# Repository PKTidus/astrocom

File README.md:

# A.S.T.R.O.COM. - Advanced Solar Tracking and Rover Observation Communication

The ASTROCOM project, developed in collaboration with the [Florida Space Institute (FSI)](https://fsi.ucf.edu/), addresses the challenge of exploring permanently shaded regions on the lunar surface. Comprising of heliostat and communication beacon towers, ASTROCOM enables wireless transmission of power and information to and from rovers within these shaded areas. The Heliostat tower utilize a reflector to redirect sunlight into the craters, powering solar assets and illuminating shaded regions, while also enabling a communication network. A portable communication beacon, intended to be deployed by rovers, a facilitate communication between the heliostat towers and rovers, overcoming obstacles within the craters.
Heliostat Tower             |  Communication Beacon
:-------------------------:|:-------------------------:
  |  

**Project Members:**  
Alex Fiset (Power/PCB)  
Pedro Kasprzykowski (Wireless/Website)  
Stephen Martin (Sensors/Solar Tracking)  
Binh Pham (Project Lead/Motors)  

**Special Thanks:**  
Dr. Chung Yong Chan  
Dr. Arthur Weeks  

**This project was sponsored by the [Florida Space Institute](https://fsi.ucf.edu/)**  

**This project was made as a [University of Central Florida Electrical and Computer Engineering Department](https://www.ece.ucf.edu/) Senior Design project throughout the Fall 2023 - Spring 2024 term**

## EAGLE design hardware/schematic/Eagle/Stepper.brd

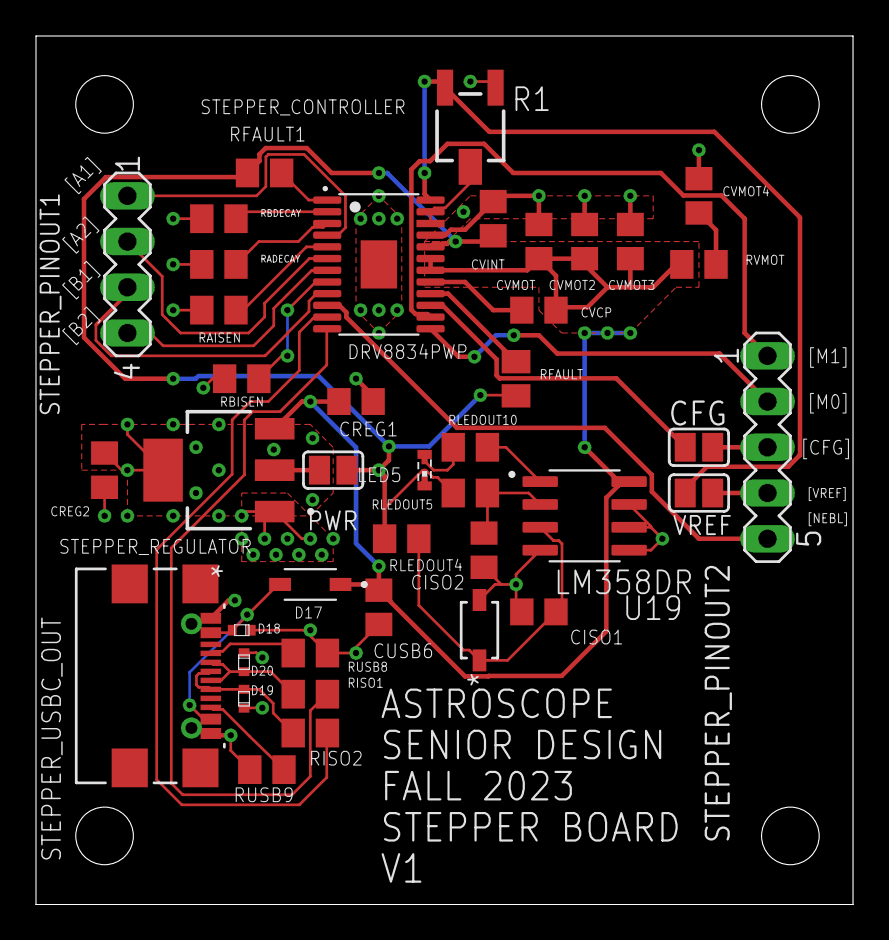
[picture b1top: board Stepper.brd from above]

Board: 2 copper layers, 45.4 x 48.2 mm, 41 parts (0 on the bottom side), 35 nets.

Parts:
CFG: SJ
CISO1, CISO2: 0.01uF; C0805
CREG1: 10uF; C0805
CREG2: 22uF; C0805
CUSB6: 10uF; C0805
CVCP: 0.01uF; C0805
CVINT: 4.7uF; C0805
CVMOT, CVMOT4: 10uF; C0805
CVMOT2, CVMOT3: 0.1uF; C0805
D17: 1N5819HW-7-F; SOD3715X145N
D18, D19, D20: CPDQ5V0-HF; MBTB-D-SOD-923F-IMP-0402
LED5: SMARTLED-TTW
PWR: SJ
R1: 10k; 3223G
RADECAY: 47k; M0805
RAISEN: 0.1; M0805
RBDECAY: 47k; M0805
RBISEN: 0.1; M0805
RFAULT: 1.5k; M0805
RFAULT1: 10k; M0805
RISO1, RISO2: 1.5k; M0805
RLEDOUT4, RLEDOUT5: 10k; M0805
RLEDOUT10: 2.2k; M0805
RUSB8, RUSB9: 5.1k; M0805
RVMOT: 1; M0805
STEPPER_CONTROLLER: DRV8834PWP; SOP65P640X120-25N
STEPPER_PINOUT1: MA04-1
STEPPER_PINOUT2: MA05-1
STEPPER_REGULATOR: AZ1117IH-3.3TRG1; SOT230P700X185-4N
STEPPER_USBC_OUT: USB4110-GF-A; USB4110-GF-A_GCT
U16: MMSZ5225BT1G; SOD-123_ONS
U19: LM358DR; SOIC127P599X175-8N
VREF: SJ

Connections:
3.3VOUTUSB2: CVINT.1, LED5.A@1, PWR.2, RFAULT.2, RFAULT1.1, RLEDOUT4.2, RLEDOUT5.2, STEPPER_CONTROLLER.20
3.3VREGOUT: CREG2.1, PWR.1, STEPPER_REGULATOR.2, STEPPER_REGULATOR.4
5VOUTUSB2: CREG1.1, CUSB6.1, CVCP.1, CVMOT.2, CVMOT2.2, CVMOT3.2, D17.C, RVMOT.2, STEPPER_CONTROLLER.18, STEPPER_CONTROLLER.19, STEPPER_REGULATOR.3, U19.8
AOUT1: STEPPER_CONTROLLER.4, STEPPER_PINOUT1.1
AOUT2: STEPPER_CONTROLLER.6, STEPPER_PINOUT1.2
BOUT1: STEPPER_CONTROLLER.9, STEPPER_PINOUT1.3
BOUT2: STEPPER_CONTROLLER.7, STEPPER_PINOUT1.4
CONFIGOUT: CFG.1, STEPPER_PINOUT2.3
GND: CISO1.2, CISO2.2, CREG1.2, CREG2.2, CUSB6.2, CVINT.2, CVMOT.1, CVMOT2.1, CVMOT3.1, CVMOT4.1, D18.1, D19.1, D20.1, R1.1, RADECAY.2, RAISEN.2, RBDECAY.2, RBISEN.2, RUSB8.2, RUSB9.2, STEPPER_CONTROLLER.21, STEPPER_CONTROLLER.25, STEPPER_REGULATOR.1, STEPPER_USBC_OUT.A1-B12, STEPPER_USBC_OUT.A12-B1, U16.2, U19.4, U19.5, U19.6, U19.7
GPIO8M: D19.2, RISO2.2, STEPPER_USBC_OUT.A6, STEPPER_USBC_OUT.B6
GPIO9M: D20.2, RISO1.2, STEPPER_USBC_OUT.A7, STEPPER_USBC_OUT.B7
M0OUT: STEPPER_CONTROLLER.13, STEPPER_PINOUT2.2
M1OUT: STEPPER_CONTROLLER.14, STEPPER_PINOUT2.1
unnamed: RISO1.1, STEPPER_CONTROLLER.12
unnamed: RISO2.1, STEPPER_CONTROLLER.11
unnamed: CVMOT4.2, RVMOT.1
unnamed: RBISEN.1, STEPPER_CONTROLLER.8
unnamed: RAISEN.1, STEPPER_CONTROLLER.5
unnamed: RBDECAY.1, STEPPER_CONTROLLER.2
unnamed: RADECAY.1, STEPPER_CONTROLLER.3
unnamed: RFAULT.1, STEPPER_CONTROLLER.16
unnamed: CVCP.2, STEPPER_CONTROLLER.17
unnamed: R1.2, STEPPER_CONTROLLER.22, STEPPER_CONTROLLER.23
unnamed: CFG.2, STEPPER_CONTROLLER.15
unnamed: RUSB8.1, STEPPER_USBC_OUT.A5
unnamed: RUSB9.1, STEPPER_USBC_OUT.B5
unnamed: CISO1.1, RLEDOUT4.1, U16.1, U19.3
unnamed: CISO2.1, RLEDOUT5.1, U19.2
unnamed: RLEDOUT10.2, U19.1
unnamed: LED5.C@1, RLEDOUT10.1
NENBL: STEPPER_CONTROLLER.10, STEPPER_PINOUT2.5
SLP: RFAULT1.2, STEPPER_CONTROLLER.1
VBUS22: D17.A, D18.2, STEPPER_USBC_OUT.A4-B9, STEPPER_USBC_OUT.A9-B4
VREF: R1.3, STEPPER_CONTROLLER.24, VREF.2
VREFOUT: STEPPER_PINOUT2.4, VREF.1

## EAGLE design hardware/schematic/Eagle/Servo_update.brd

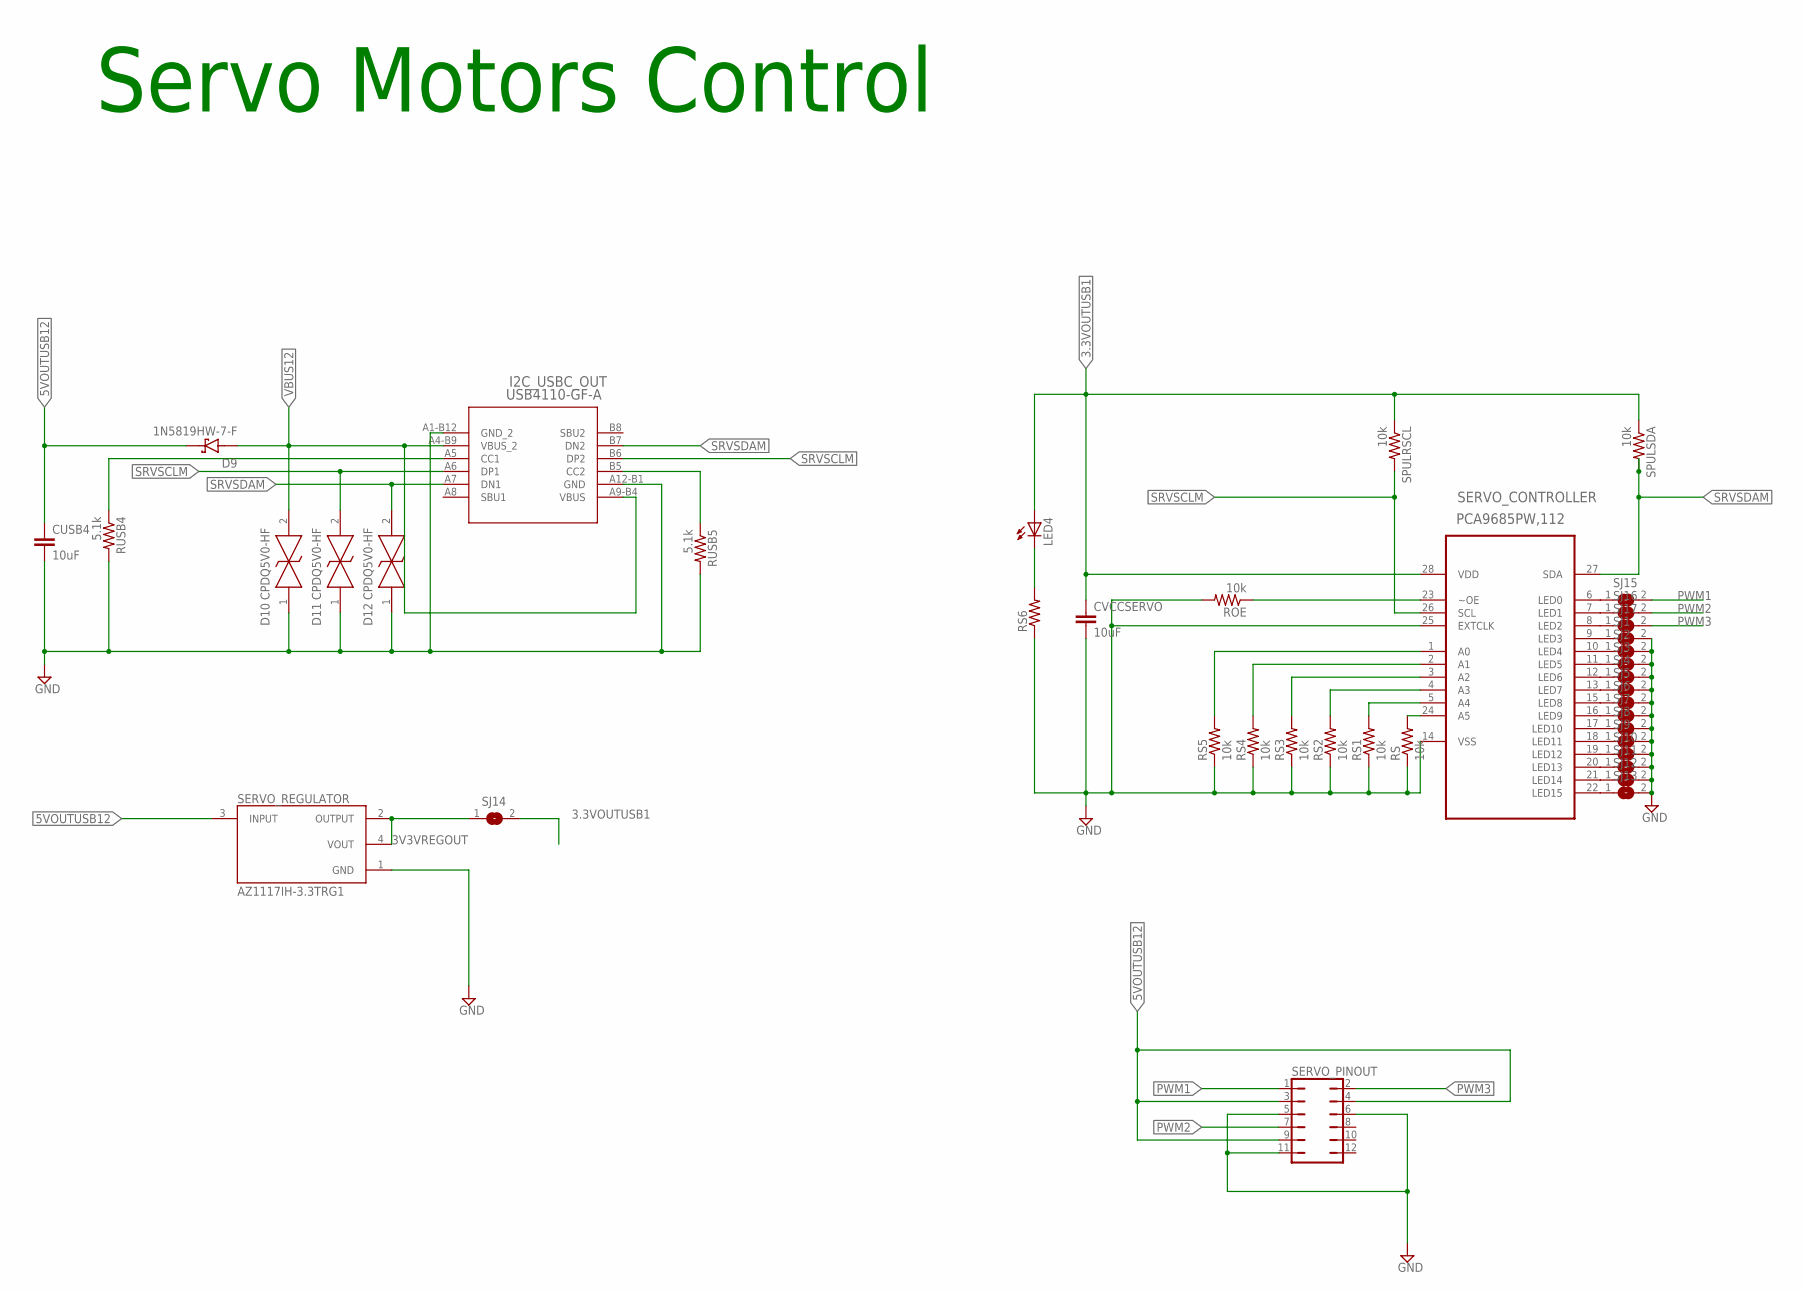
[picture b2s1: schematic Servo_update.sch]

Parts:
CUSB4: 10uF; C0805
CVCCSERVO: 10uF; C0805
D9: 1N5819HW-7-F; SOD3715X145N
D10, D11, D12: CPDQ5V0-HF; MBTB-D-SOD-923F-IMP-0402
I2C_USBC_OUT: USB4110-GF-A; USB4110-GF-A_GCT
LED4: LED; SMARTLED-TTW
ROE: 10k; M0805
RS, RS1, RS2, RS3, RS4, RS5: 10k; R0805
RS6: 2.2k; R0805
RUSB4, RUSB5: 5.1k; M0805
SERVO_CONTROLLER: PCA9685PW,112; SOP65P640X110-28N
SERVO_PINOUT: JP6Q
SERVO_REGULATOR: AZ1117IH-3.3TRG1; SOT230P700X185-4N
SJ1, SJ2, SJ3, SJ4, SJ5, SJ6, SJ7, SJ8, SJ9, SJ10, SJ11, SJ12, SJ13, SJ14, SJ15, SJ16, SJ17: SJ
SPULRSCL: 10k; M0805
SPULSDA: 10k; M0805

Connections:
3.3VOUTUSB1: CVCCSERVO.1, LED4.A@1 (A), SERVO_CONTROLLER.28 (VDD), SJ14.2, SPULRSCL.1, SPULSDA.1
3V3VREGOUT: SERVO_REGULATOR.2 (OUTPUT), SERVO_REGULATOR.4 (VOUT), SJ14.1
5VOUTUSB12: CUSB4.1, D9.C (K), SERVO_PINOUT.3, SERVO_PINOUT.4, SERVO_PINOUT.9, SERVO_REGULATOR.3 (INPUT)
A0: RS5.2, SERVO_CONTROLLER.1 (A0)
A1: RS4.2, SERVO_CONTROLLER.2 (A1)
A2: RS3.2, SERVO_CONTROLLER.3 (A2)
A3: RS2.2, SERVO_CONTROLLER.4 (A3)
A4: RS1.2, SERVO_CONTROLLER.5 (A4)
A5: RS.2, SERVO_CONTROLLER.24 (A5)
CC1_RUSB4: I2C_USBC_OUT.A5 (CC1), RUSB4.1
CC2: I2C_USBC_OUT.B5 (CC2), RUSB5.1
GND: CUSB4.2, CVCCSERVO.2, D10.1 (K), D11.1 (K), D12.1 (K), I2C_USBC_OUT.A1-B12 (GND_2), I2C_USBC_OUT.A12-B1 (GND), ROE.2, RS.1, RS1.1, RS2.1, RS3.1, RS4.1, RS5.1, RS6.1, RUSB4.2, RUSB5.2, SERVO_CONTROLLER.14 (VSS), SERVO_CONTROLLER.25 (EXTCLK), SERVO_PINOUT.5, SERVO_PINOUT.6, SERVO_PINOUT.11, SERVO_REGULATOR.1 (GND), SJ1.2, SJ2.2, SJ3.2, SJ4.2, SJ5.2, SJ6.2, SJ7.2, SJ8.2, SJ9.2, SJ10.2, SJ11.2, SJ12.2, SJ13.2
LED_RS6: LED4.C@1 (C), RS6.2
unnamed: SERVO_CONTROLLER.9 (LED3), SJ1.1
unnamed: SERVO_CONTROLLER.10 (LED4), SJ2.1
unnamed: SERVO_CONTROLLER.11 (LED5), SJ3.1
unnamed: SERVO_CONTROLLER.12 (LED6), SJ4.1
unnamed: SERVO_CONTROLLER.13 (LED7), SJ5.1
unnamed: SERVO_CONTROLLER.15 (LED8), SJ6.1
unnamed: SERVO_CONTROLLER.16 (LED9), SJ7.1
unnamed: SERVO_CONTROLLER.18 (LED11), SJ9.1
unnamed: SERVO_CONTROLLER.19 (LED12), SJ10.1
unnamed: SERVO_CONTROLLER.20 (LED13), SJ11.1
unnamed: SERVO_CONTROLLER.21 (LED14), SJ12.1
unnamed: SERVO_CONTROLLER.17 (LED10), SJ8.1
unnamed: SERVO_CONTROLLER.22 (LED15), SJ13.1
unnamed: SERVO_CONTROLLER.6 (LED0), SJ15.1
unnamed: SERVO_CONTROLLER.7 (LED1), SJ16.1
unnamed: SERVO_CONTROLLER.8 (LED2), SJ17.1
OE: ROE.1, SERVO_CONTROLLER.23 (~OE)
PWM1: SERVO_PINOUT.1, SJ15.2
PWM2: SERVO_PINOUT.7, SJ16.2
PWM3: SERVO_PINOUT.2, SJ17.2
SRVSCLM: D11.2 (A), I2C_USBC_OUT.A6 (DP1), I2C_USBC_OUT.B6 (DP2), SERVO_CONTROLLER.26 (SCL), SPULRSCL.2
SRVSDAM: D12.2 (A), I2C_USBC_OUT.A7 (DN1), I2C_USBC_OUT.B7 (DN2), SERVO_CONTROLLER.27 (SDA), SPULSDA.2
VBUS12: D9.A, D10.2 (A), I2C_USBC_OUT.A4-B9 (VBUS_2), I2C_USBC_OUT.A9-B4 (VBUS)

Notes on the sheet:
Servo Motors Control

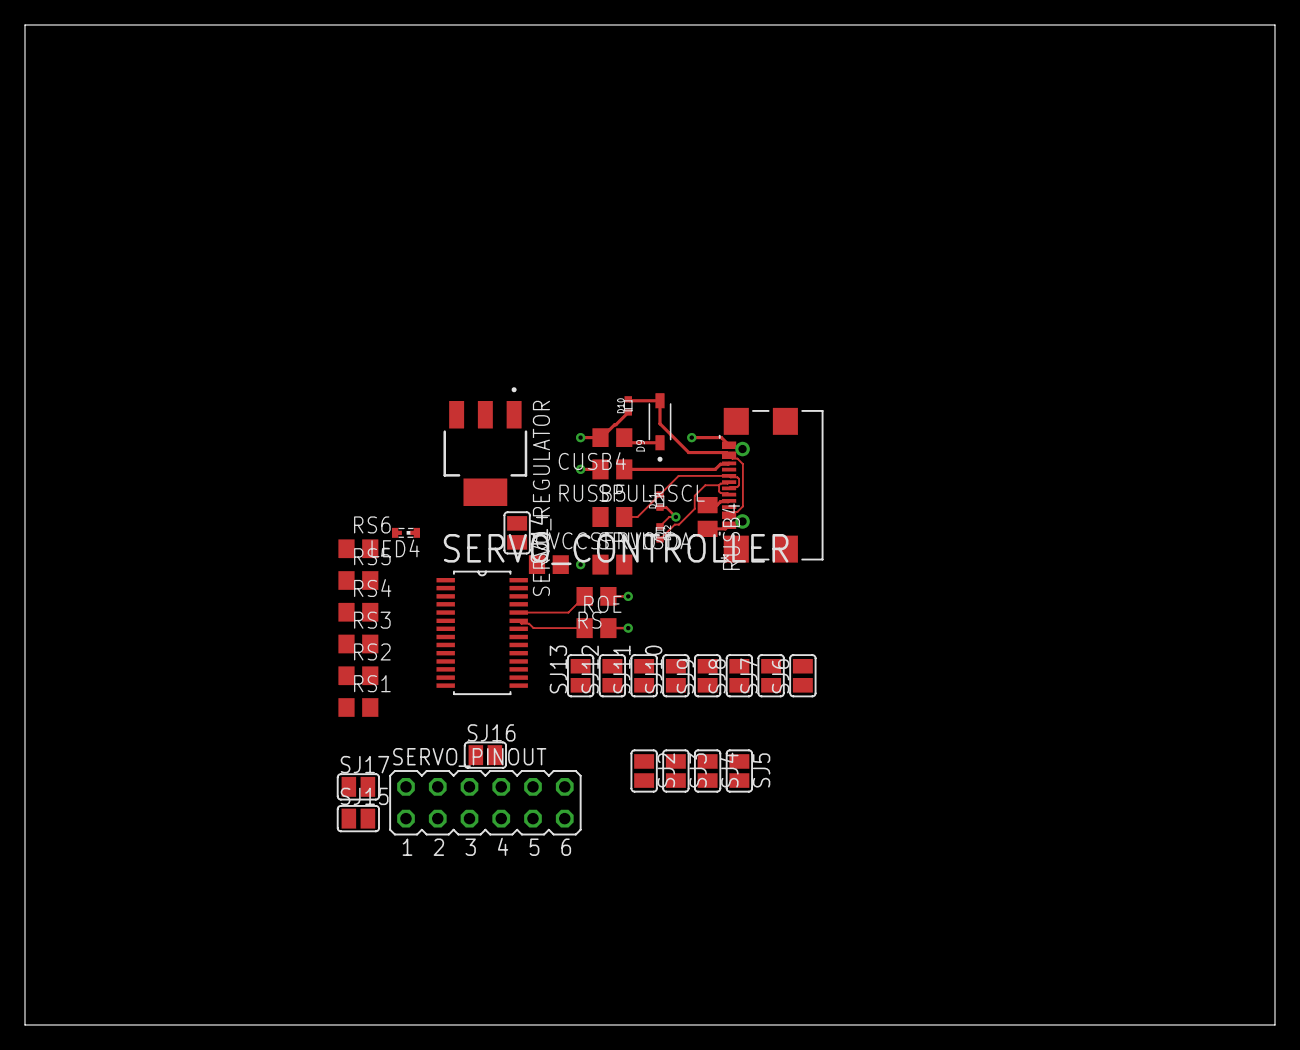
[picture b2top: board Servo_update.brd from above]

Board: 2 copper layers, 100.0 x 80.0 mm, 40 parts (1 on the bottom side), 36 nets.

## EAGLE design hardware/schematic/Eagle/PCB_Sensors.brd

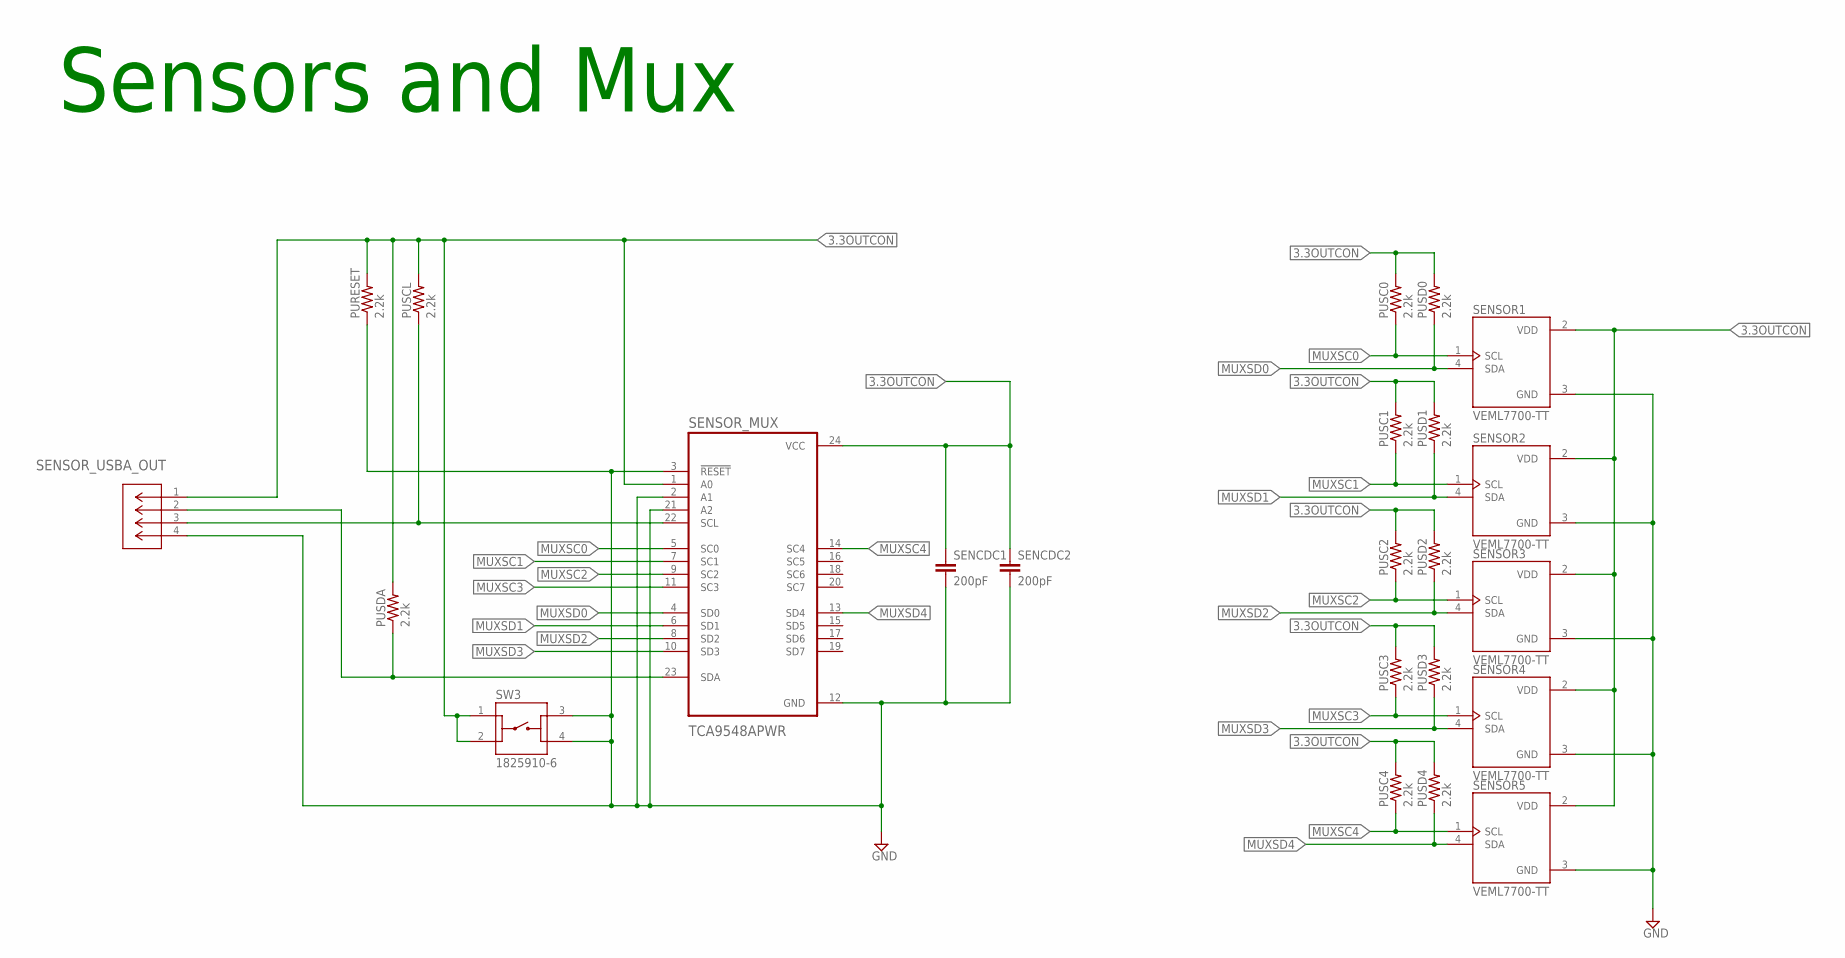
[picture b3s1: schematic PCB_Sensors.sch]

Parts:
PURESET: 2.2k; M0805
PUSC0, PUSC1, PUSC2, PUSC3, PUSC4: 2.2k; M0805
PUSCL: 2.2k; M0805
PUSD0, PUSD1, PUSD2, PUSD3, PUSD4: 2.2k; M0805
PUSDA: 2.2k; M0805
SENCDC1, SENCDC2: 200pF; C0805
SENSOR1, SENSOR2, SENSOR3, SENSOR4, SENSOR5: VEML7700-TT; XDCR_VEML7700-TT
SENSOR_MUX: TCA9548APWR; SOP65P640X120-24N
SENSOR_USBA_OUT: USB-AP-S-RA-SMT; CONN_USB-AP-S-RA-SMT_ADM
SW3: 1825910-6; SW_1825910-6-4

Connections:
3.3OUTCON: PURESET.2, PUSC0.2, PUSC1.2, PUSC2.2, PUSC3.2, PUSC4.2, PUSCL.2, PUSD0.2, PUSD1.2, PUSD2.2, PUSD3.2, PUSD4.2, PUSDA.2, SENCDC1.1, SENCDC2.1, SENSOR1.2 (VDD), SENSOR2.2 (VDD), SENSOR3.2 (VDD), SENSOR4.2 (VDD), SENSOR5.2 (VDD), SENSOR_MUX.1 (A0), SENSOR_MUX.24 (VCC), SENSOR_USBA_OUT.1, SW3.1, SW3.2
GND: PURESET.1, SENCDC1.2, SENCDC2.2, SENSOR1.3 (GND), SENSOR2.3 (GND), SENSOR3.3 (GND), SENSOR4.3 (GND), SENSOR5.3 (GND), SENSOR_MUX.2 (A1), SENSOR_MUX.3 (!RESET), SENSOR_MUX.12 (GND), SENSOR_MUX.21 (A2), SENSOR_USBA_OUT.4, SW3.3, SW3.4
MCUI2CSCL: PUSCL.1, SENSOR_MUX.22 (SCL), SENSOR_USBA_OUT.3
MCUI2CSDA: PUSDA.1, SENSOR_MUX.23 (SDA), SENSOR_USBA_OUT.2
MUXSC0: PUSC0.1, SENSOR1.1 (SCL), SENSOR_MUX.5 (SC0)
MUXSC1: PUSC1.1, SENSOR2.1 (SCL), SENSOR_MUX.7 (SC1)
MUXSC2: PUSC2.1, SENSOR3.1 (SCL), SENSOR_MUX.9 (SC2)
MUXSC3: PUSC3.1, SENSOR4.1 (SCL), SENSOR_MUX.11 (SC3)
MUXSC4: PUSC4.1, SENSOR5.1 (SCL), SENSOR_MUX.14 (SC4)
MUXSD0: PUSD0.1, SENSOR1.4 (SDA), SENSOR_MUX.4 (SD0)
MUXSD1: PUSD1.1, SENSOR2.4 (SDA), SENSOR_MUX.6 (SD1)
MUXSD2: PUSD2.1, SENSOR3.4 (SDA), SENSOR_MUX.8 (SD2)
MUXSD3: PUSD3.1, SENSOR4.4 (SDA), SENSOR_MUX.10 (SD3)
MUXSD4: PUSD4.1, SENSOR5.4 (SDA), SENSOR_MUX.13 (SD4)

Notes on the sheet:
Sensors and Mux

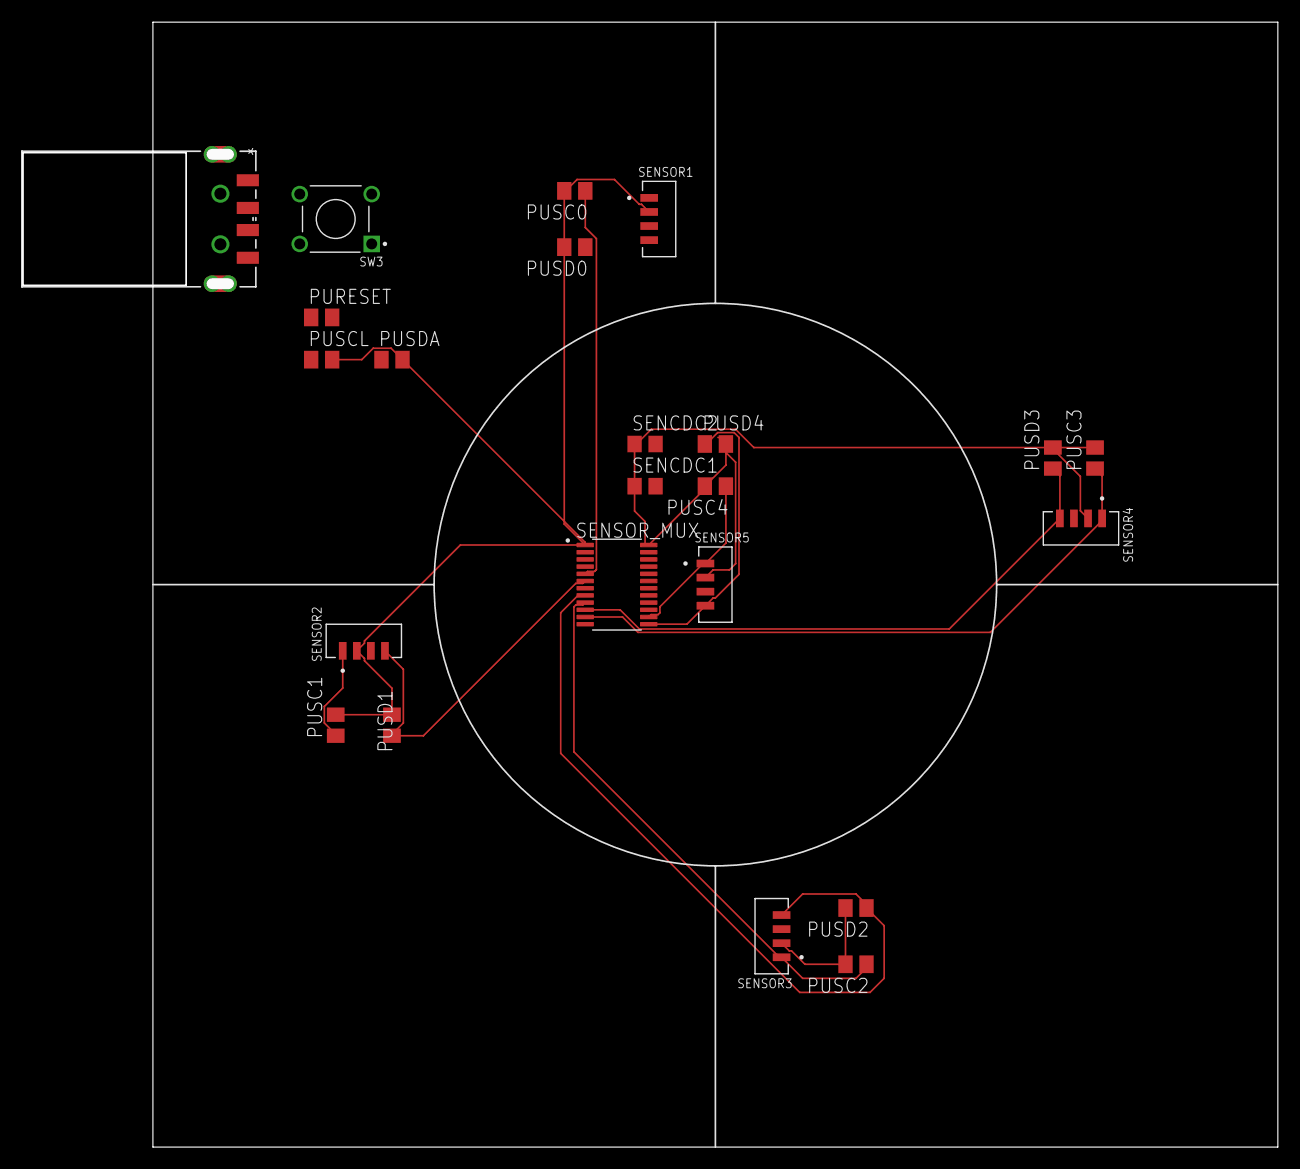
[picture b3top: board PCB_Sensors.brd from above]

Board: 2 copper layers, 112.4 x 100.6 mm, 23 parts (0 on the bottom side), 14 nets.

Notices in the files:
parts and their libraries:
USB-AP-S-RA-SMT: COPYRIGHT: Copyright (C) 2023 Ultra Librarian. All rights reserved.
